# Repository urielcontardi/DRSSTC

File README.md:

# ARCSTRIKE

A **dual-resonant solid-state Tesla coil (DRSSTC)** project combining KiCad
electronics, resonator calculations, and a parametric enclosure with a unified
lid and resonator deck.

<p align="center"><em>Enclosure and resonator overview. The current CAD incorporates the unified lid and deck.</em></p>

<p align="center"><em>Assembled PCB — explore the interactive view in the project notebook.</em></p>

**Status:** assembly prototype. Physical fits, thermal behavior, and electrical
insulation still require validation. The primary wire holder remains pending.

## Quick start

| Task | File |
| --- | --- |
| Edit the electronics | [KiCad project](hardware/pcb/oneTesla.kicad_pro) |
| Print the enclosure | [STLs and quantities](mechanical/print/) |
| Assemble the enclosure | [Assembly guide](mechanical/README.md) · [Hardware BOM](mechanical/exports/hardware-BOM.csv) |
| Open the assembly in CAD | [STEP](mechanical/exports/ASSEMBLY.step) · [SolidCraft](mechanical/ASSEMBLY.sc) |
| Review the calculations | [Coil design](docs/design/COILS.md) |
| Explore the offline documentation | [Project notebook](docs/project/PROJECT-DRSSTC.html) |
| Inspect the PCB exports | [Gerbers, reports, and STEP](hardware/pcb/exports/) |

## Repository structure

```text
hardware/pcb/    KiCad project, local libraries, and PCB exports
mechanical/      Current enclosure sources, print files, assembly, and checks
docs/            Calculations, project notebook, and technical references
scripts/         PCB and documentation tools
```

The repository contains the current project. Earlier revisions are available
through Git history. Exported files stay alongside their sources in
`hardware/pcb/exports/` and `mechanical/exports/`. Printable STLs live in
`mechanical/print/`, with quantities included in their filenames.

## Reproduce the project

Run commands from the repository root:

```sh
# Recalculate the resonator (Python 3)
python3 -B scripts/calculate_resonator.py

# Rebuild the current enclosure (uv and CadQuery)
uv run --with cadquery python mechanical/build.py

# Validate all printable meshes
python3 -B mechanical/verify_stls.py

# Build the notebook and its offline ZIP (Python 3 and Node.js)
python3 -B scripts/build_project_document.py
```

Generated ZIPs and temporary results go to `output/`, which is ignored by Git.
Rebuilding CAD updates the exported files; review the reports and diff before
committing. The existing Gerbers represent the export documented in the
[PCB export notes](hardware/pcb/exports/README.md).

## Documentation

- [Electronics and KiCad libraries](hardware/pcb/README.md)
- [Enclosure assembly and printing](mechanical/README.md)
- [Technical documentation index](docs/README.md)
- [Tools and validation commands](scripts/README.md)
- [Maintenance conventions](CONTRIBUTING.md)

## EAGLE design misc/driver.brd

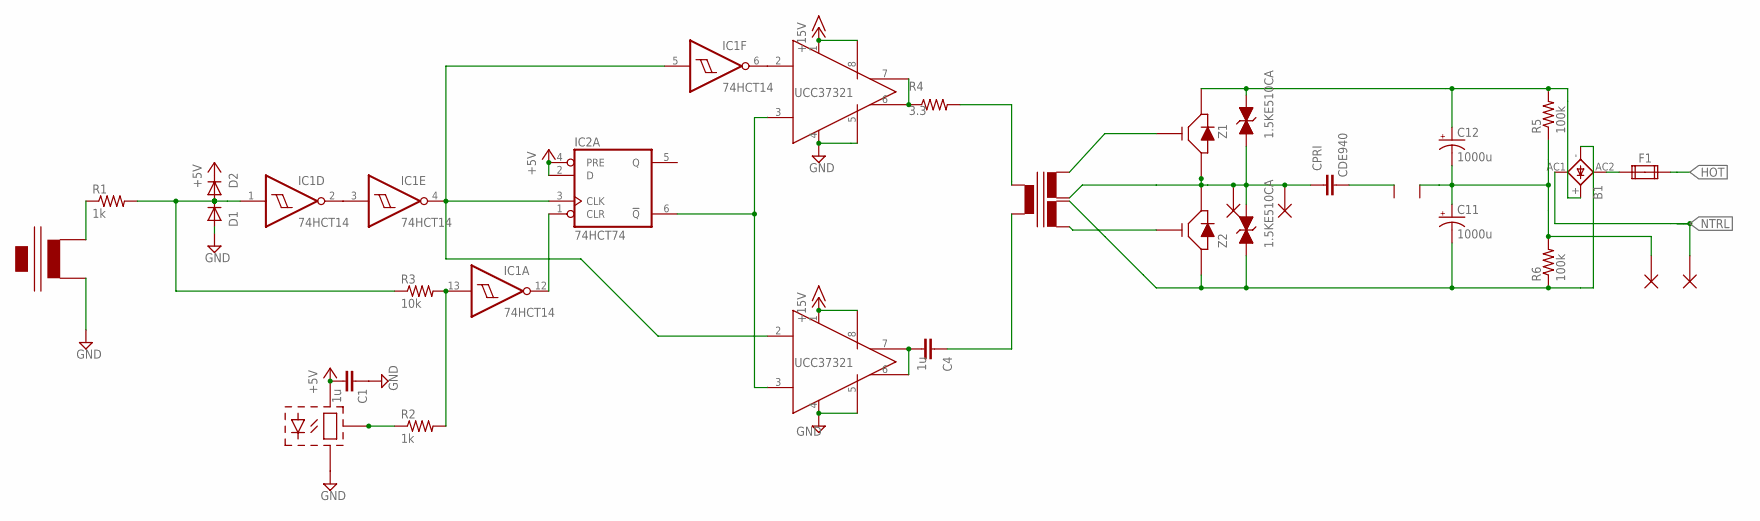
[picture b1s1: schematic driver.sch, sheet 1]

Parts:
B1: GBU4; GBU4S
C1, C4: 1u; C050-024X044@1
C11, C12: 1000u; EB25D
CPRI: CDE940
D1, D2: 1N4148DO35-7; DO35-7
F1: FUSE2P; FUSE1
IC1: 74HCT14; DIL14
IC2: 74HCT74; DIL14
IC3, IC4: UCC37321DIL8; DIL08
P1, P2, P3, P4: 12AWG_PAD
R1: 1k; 0922/22
R2: 1k; 0204/7
R3: 10k; 0204/7
R4: 3.3; 0204/7
R5, R6: 100k; 0309/10
T1: P0584
U$2: TRIAD_CT; CT2
U$5: 2STANDOFFS
U$6: IF-D95; IFD95
U$7, U$8: FGA60N65SMD; TO247H
Z1, Z2: 1.5KE510CA; DO201

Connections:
+5V: C1.2, D2.C, IC2.2 (D), IC2.4 (PRE), U$6.V+ (VCC); also elsewhere on the board
+15V: IC3.1 (1_VDD), IC3.8 (8_VDD), IC4.1 (1_VDD), IC4.8 (8_VDD); also elsewhere on the board
GND: C1.1, D1.A, IC3.4 (4_AGND), IC3.5 (5_PGND), IC4.4 (4_AGND), IC4.5 (5_PGND), U$2.P$2, U$6.GND; also elsewhere on the board
HOT: F1.2A; also elsewhere on the board
N: C11.+, C12.-, P3.P$1, R5.1, R6.2, U$5.P$1
unnamed: R1.1, U$2.P$1
unnamed: T1.7 (SEC2B), U$8.G
unnamed: D1.C, D2.A, IC1.1 (I), R1.2, R3.1
unnamed: IC1.6 (O), IC3.2 (2_IN)
unnamed: IC1.2 (O), IC1.3 (I)
unnamed: IC1.12 (O), IC2.1 (CLR)
unnamed: IC3.6 (6_OUT), IC3.7 (7_OUT), R4.1
unnamed: C4.2, IC4.6 (6_OUT), IC4.7 (7_OUT)
unnamed: CPRI.P$1 (1), P1.P$1, P2.P$1, T1.4 (SEC1B), U$7.E, U$8.C, Z1.A, Z2.C
unnamed: R2.1, U$6.OUT
unnamed: IC1.13 (I), R2.2, R3.2
unnamed: B1.AC2 (AC1), F1.1A
unnamed: T1.3 (SEC1A), U$7.G
unnamed: IC1.4 (O), IC1.5 (I), IC2.3 (CLK), IC4.2 (2_IN)
unnamed: CPRI.P$2 (2), U$5.P$2
unnamed: R4.2, T1.1 (PRIA)
unnamed: C4.1, T1.10 (PRIB)
unnamed: IC2.6 (!Q), IC3.3 (3_ENBL), IC4.3 (3_ENBL)
NEG: B1.-, C11.-, R6.1, T1.8 (SEC2A), U$8.E, Z2.A
NTRL: B1.AC1 (AC2), P4.P$1; also elsewhere on the board
POS: B1.+, C12.+, R5.2, U$7.C, Z1.C

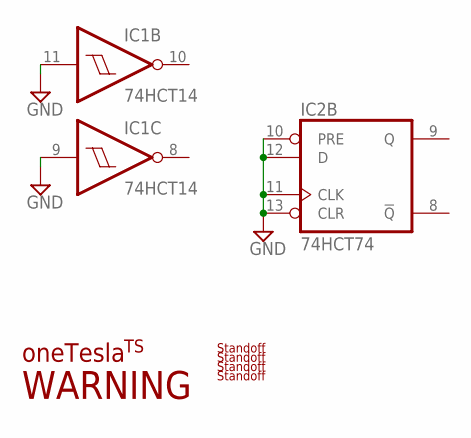
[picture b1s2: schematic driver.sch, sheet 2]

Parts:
IC1: 74HCT14; DIL14
IC2: 74HCT74; DIL14
U$1: LOGO
U$3: WARNING
U$4: TS-LOGO; TSLOGO
U$12, U$13, U$14, U$15: STANDOFF-QTR; STANDOFF

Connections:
GND: IC1.9 (I), IC1.11 (I), IC2.10 (PRE), IC2.11 (CLK), IC2.12 (D), IC2.13 (CLR); also elsewhere on the board

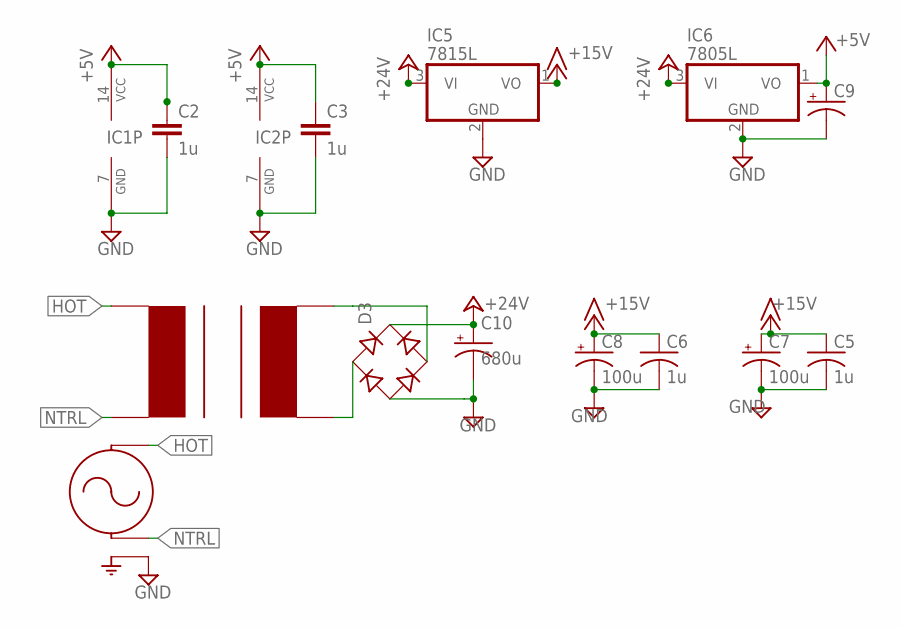
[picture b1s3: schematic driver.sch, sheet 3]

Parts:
C2, C3: 1u; C050-024X044@1
C5, C6: 1u; C050-024X044
C7, C8: 100u; E2,5-5
C9: CPOL-USE2.5-5; E2,5-5
C10: 680u; E3,5-8
D3: B-DIL
IC1: 74HCT14; DIL14
IC2: 74HCT74; DIL14
IC5: 7815L; TO92
IC6: 7805L; TO92
U$9: EI30; EL30
U$10: IEC320/C6

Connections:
+5V: C2.1, C3.1, C9.+, IC1.14 (VCC), IC2.14 (VCC), IC6.1 (VO); also elsewhere on the board
+15V: C5.1, C6.1, C7.+, C8.+, IC5.1 (VO); also elsewhere on the board
+24V: C10.+, D3.+, IC5.3 (VI), IC6.3 (VI)
GND: C2.2, C3.2, C5.2, C6.2, C7.-, C8.-, C9.-, C10.-, D3.-, IC1.7 (GND), IC2.7 (GND), IC5.2 (GND), IC6.2 (GND), U$10.G; also elsewhere on the board
HOT: U$9.1, U$10.H; also elsewhere on the board
unnamed: D3.AC1, U$9.9
unnamed: D3.AC2, U$9.7
NTRL: U$9.5, U$10.N; also elsewhere on the board

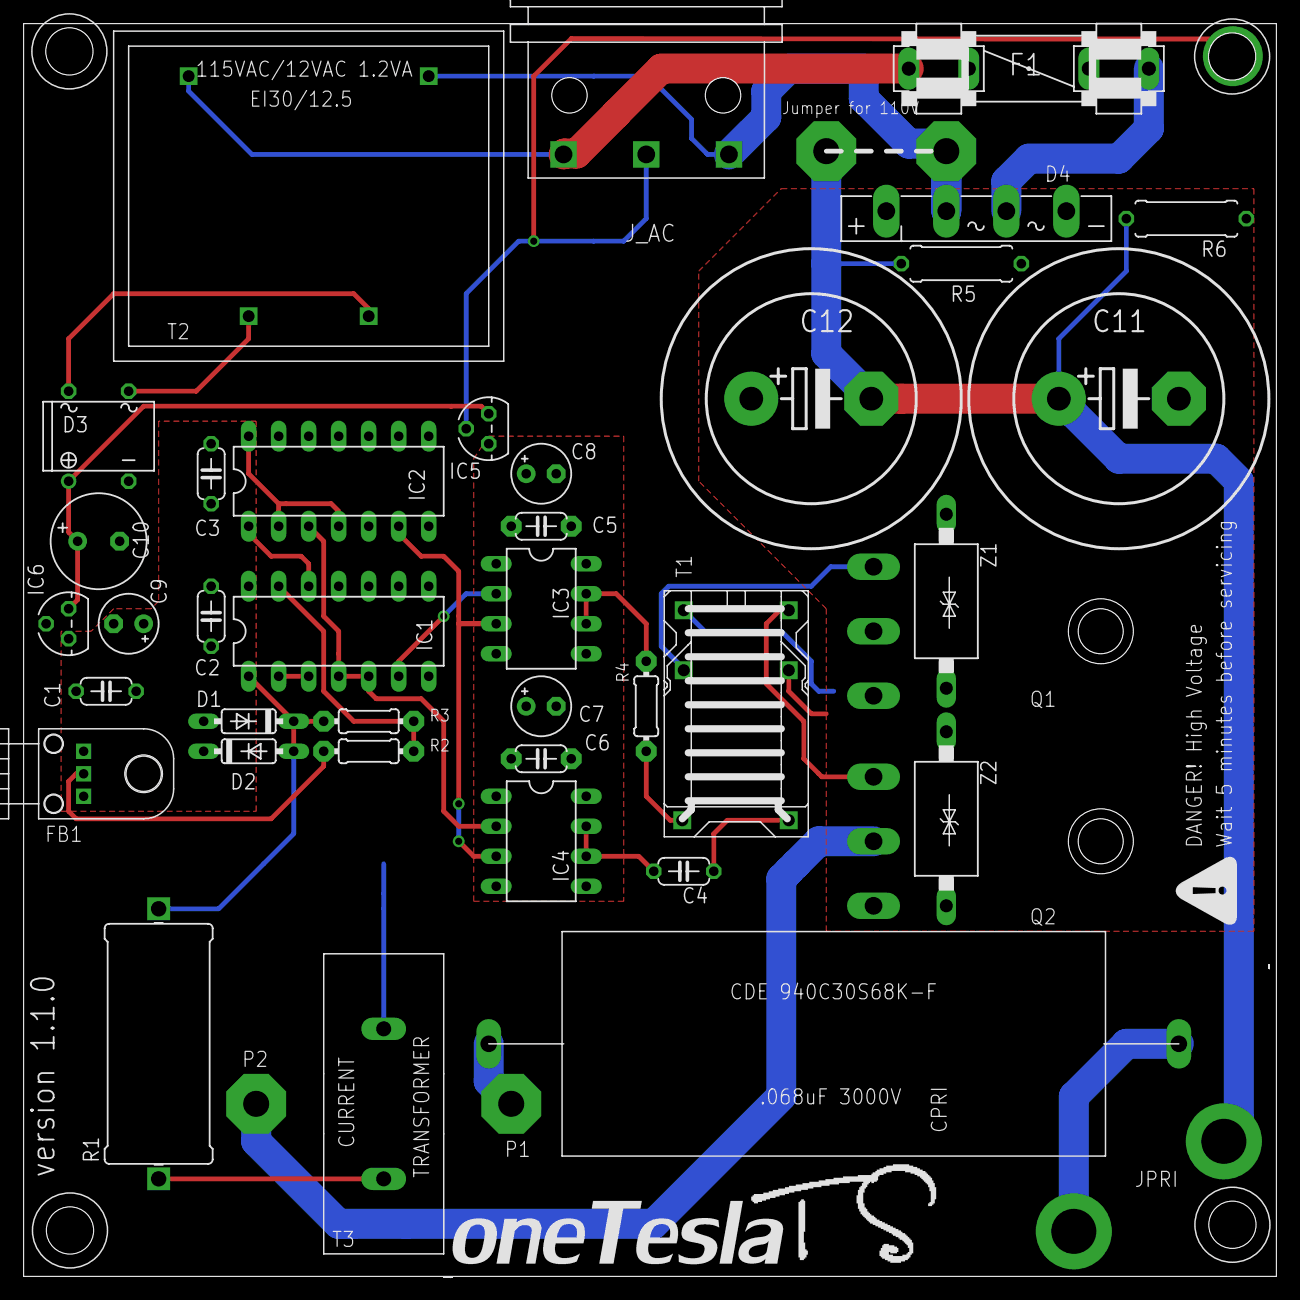
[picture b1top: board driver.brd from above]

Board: 3 copper layers, 106.0 x 106.0 mm, 51 parts (0 on the bottom side), 29 nets.
